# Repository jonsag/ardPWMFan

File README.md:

# ardPWMFan
An arduino controls a fan with PWM from temperature readings with a DS18B20

Contains sketch and CADs

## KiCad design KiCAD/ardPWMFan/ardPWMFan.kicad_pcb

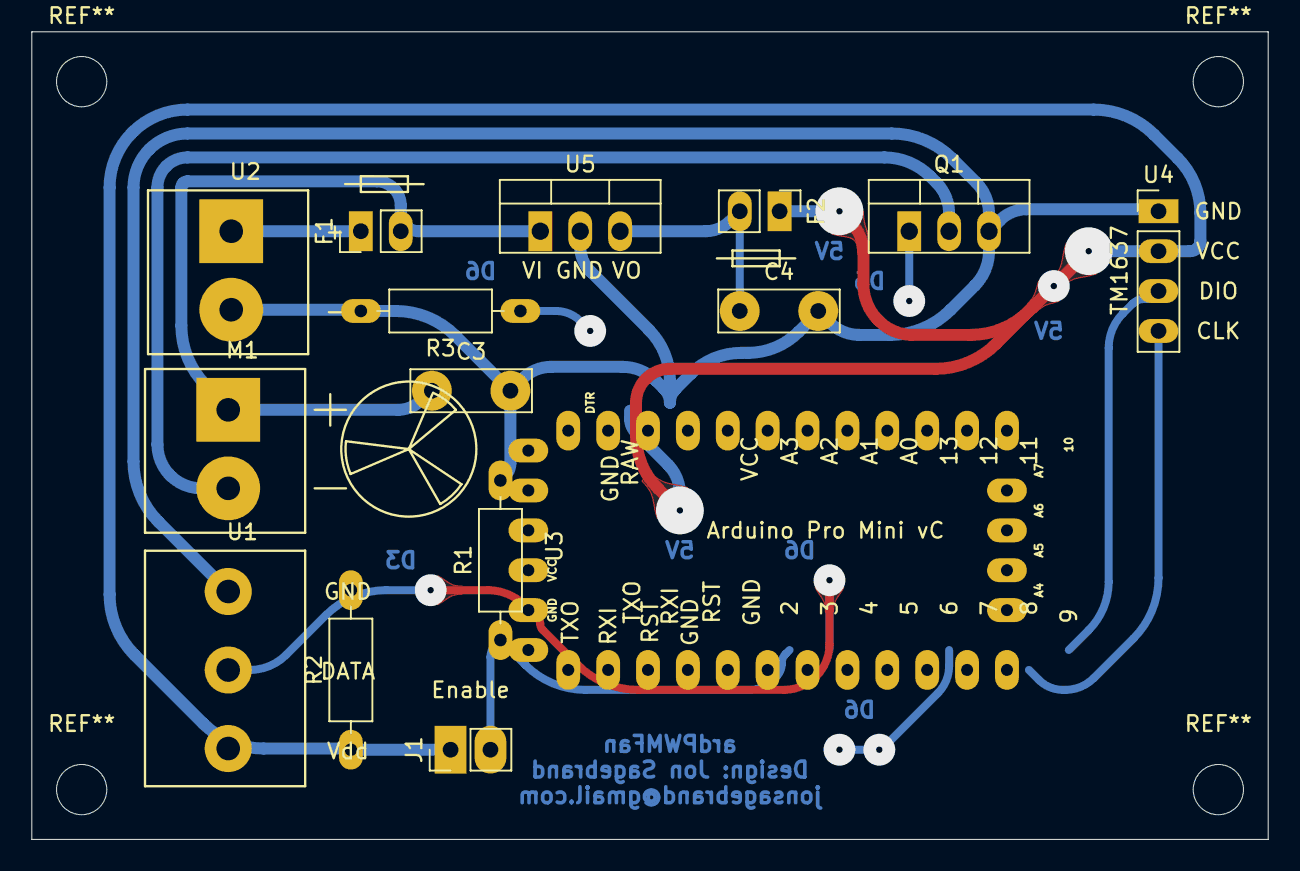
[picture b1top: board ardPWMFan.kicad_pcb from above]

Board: 2 copper layers, 78.7 x 51.4 mm, 15 parts (0 on the bottom side), 11 nets.

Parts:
C3: 0.22u; C_Disc_D7.5mm_W2.5mm_P5.00mm_larger
C4: 0.1u; C_Disc_D7.5mm_W2.5mm_P5.00mm_larger
F1, F2: Fuse; 2-pin_Fuse_header_large
J1: Conn_01x02; 2-pin_enable_header_large
M1: Fan; 2-pole_Fan_power_screw_terminal
Q1: 20N6003; TO-220-3_Vertical_larger
R1, R3: 10k; R_Axial_DIN0207_L6.3mm_D2.5mm_P10.16mm_Horizontal_larger_pa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
R2: 4.7k; R_Axial_DIN0207_L6.3mm_D2.5mm_P10.16mm_Horizontal_larger_pa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
U1: DS18B20; 3-pole_DS18B20_screw_terminal
U2: 2-pole_power_in_screw_terminal
U3: Arduino_Mini_Pro; Arduino_Pro_Mini_vC_larger_pads
U4: TM1637_4x7-segment_display; 4-pin_TM1637_header_large
U5: L7805; LM7805_TO-220-3_Vertical_larger

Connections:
+5V: F2.1, J1.1, R2.1, U1.3, U3.13, U4.2
+12V: F1.1, U2.1
+12Vf: C3.1, F1.2, M1.1, U5.1
GND: C3.2, C4.2, Q1.3, R1.2, R3.2, U1.1, U2.2, U3.14, U4.1, U5.2
unnamed: C4.1, F2.2, U5.3
unnamed: J1.2, R1.1, U3.5
unnamed: M1.2, Q1.2
unnamed: Q1.1, R3.1, U3.9
unnamed: R2.2, U1.2, U3.6
unnamed: U3.11, U4.4
unnamed: U3.12, U4.3

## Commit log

2021-01-20 readme
2021-01-20 working...
2021-01-20 updated sketch
2021-01-21 output on screen
2022-05-13 kicad6
